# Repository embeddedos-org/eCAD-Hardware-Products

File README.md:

# eCAD Hardware Products

Hardware / PCB CAD design collection for the **EmbeddedOS (EoS)** ecosystem.
The repository organizes hardware product designs by application domain. Each
domain holds one or more product lines, and each product line typically carries
a product datasheet, a bill of materials (`bom.csv`), power-budget simulation
scripts, and placeholder directories for PCB and mechanical CAD artifacts.
Several product lines also include KiCad schematics (`*.kicad_sch`).

> Status varies by design. Directories are at different maturity levels (many
> "Design" / "Pre-production"); PCB and CAD folders often contain `.gitkeep`
> placeholders rather than finished layouts. Check each design's own `README.md`
> and `docs/` for its current state.

## Domains

The repository contains **16** domain design collections:

| Domain | Focus |
|---|---|
| `eAerospace_CAD_Design` | Aircraft components, avionics, UAV/drone systems, space systems |
| `eConsumer_CAD_Design` | Smart home devices, personal wearables, AR/smart devices |
| `eCybersecurity_CAD_Design` | Security appliances and physical security systems |
| `eDefense_CAD_Design` | Surveillance, tactical communications, protection equipment |
| `eElectronics_CAD_Design` | PCBs, embedded controllers, RF modules, FPGAs, AI accelerators |
| `eEnergy_CAD_Design` | Battery products, renewable energy systems, power electronics |
| `eHealth365_CAD_Design` | Two-device health monitoring system (smart patch / smart ring) |
| `eIndustrial_CAD_Design` | Sensors, industrial electronics, infrastructure equipment |
| `eMedical_CAD_Design` | Diagnostic, surgical, patient-care, laboratory equipment |
| `eMining_CAD_Design` | Autonomous mining/construction equipment, industrial safety systems |
| `ePAM_CAD_Design` | Personal air/ground mobility — solar-hybrid transport, 4-product line |
| `eRadar360_CAD_Design` | 360° automotive safety radar + laser + V2X + AI threat detection |
| `eRobotics_CAD_Design` | Industrial robots, autonomous systems, robot components |
| `eSmartCity_CAD_Design` | Urban infrastructure, utilities, telecommunications |
| `eTransport_CAD_Design` | Automotive electronics, rail systems, maritime systems |
| `eosHealth_CAD_Design` | Four-device wearable health platform |

Plus:

- `future_designs/` — early/prospective concepts (e.g. `eBCI-Lite`)
- `docs/` — repository-level documentation

## Typical design layout

Most domains follow a common structure, for example:

```
eAerospace_CAD_Design/
  README.md
  docs/                      business_plan.md, regulatory_path.md
  ebuild_simulation/         eBuild simulation notes
  <product_line>/
    product_datasheet.md
    bom.csv
    simulation/power_budget_sim.py
    hardware/
      pcb/  cad/  antenna/   (artifact folders; often .gitkeep placeholders)
```

Artifact formats present in the repo include Markdown datasheets, CSV BOMs,
Python simulation scripts, and KiCad schematics (`*.kicad_sch`). Some product
lines also include TypeScript/Dart companion app sources and 3D-model notes.

## Simulations

Power-budget simulations are plain Python scripts, runnable per product line:

```bash
cd eAerospace_CAD_Design/<product_line>/simulation/
python3 power_budget_sim.py
```

Design docs reference the [EoSim](https://github.com/embeddedos-org/EoSim)
digital-twin platform for hardware-in-the-loop testing. Running one script alone
does not establish that a product is validated.

## Evidence-backed product validation

The committed `tools/catalog/product_inventory.json` is the complete product
execution set. The v1 contract schemas and policy requirements are documented in
`docs/hardware-validation-contract-v1.md`.

Discover inventory drift and inspect local tool capabilities:

```bash
python3 tools/validate_products.py discover
python3 tools/validate_products.py capabilities
```

Execute V0-V4 for every inventoried product and write hash-bound receipts:

```bash
python3 tools/validate_products.py validate \
  --all \
  --output /tmp/ecad-validation \
  --mode evidence
python3 tools/validate_products.py verify-bundle \
  /tmp/ecad-validation/bundle.json
```

`--mode evidence` succeeds when the selected inventory was executed and valid
receipts were written. Individual products may still be honestly `FAIL`,
`BLOCKED`, `INCONCLUSIVE`, or `NOT_RUN`. Use `--mode gate` for a release check;
it succeeds only when every selected product has real `PASS` evidence for V0,
V1, V2, V3, and V4. Historical baseline entries never waive a failed or missing
requirement.

## License

MIT — see [LICENSE](LICENSE).

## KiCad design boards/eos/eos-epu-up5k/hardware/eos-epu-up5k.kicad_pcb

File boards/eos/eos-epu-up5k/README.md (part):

# EoS EPU Board

An original iCE40UP5K FPGA board for EPU, EmbeddedOS's RISC-V SoC: 75 × 55 mm, four layers.
Designed by Kartikeydheer Srivastava.
All rights reserved: not open source, and not under this repository's MIT licence.
Anyone may view it, clone this repository and run its tests; anything more needs
Kartikeydheer Srivastava's written permission (kartikeydheer@gmail.com). EmbeddedOS (EoS) Research Foundation has a limited, revocable
permission. See [LICENSE.txt](LICENSE.txt) and [the licence summary](../README.md#licence).

A board for the same job as a bought iCE40UP5K development board; an original design, not a copy:
no file of any vendor's board was used. No schematic, layout, CAD, Gerber or BOM of Lattice's
evaluation or breakout boards, of any other iCE40 board (iCEBreaker, UPduino, pico-ice) or of an FTDI
module was opened. The circuit comes from the chips' data sheets and application notes, the
FT2232H pin roles from the source code of the open-source programmers that use them (iceprog and
openFPGALoader), and the Pmod ports from Digilent's published Pmod Interface Specification.

| | |
|---|---|
|  |  |

One USB-C cable powers the board, programs the FPGA's configuration flash and carries EPU's serial
console. The FPGA pins are laid out for EPU's FPGA top (`epu/fpga/ice40/epu_ice40_top.v`); the
[pin table](#pin-table) maps every one of the FPGA's 39 user pins, and EPU's pin file is written from it.
EPU's source is not yet published.

## What is on it

| Block | Parts, values and source |
|---|---|
| FPGA | Lattice iCE40UP5K-SG48I (5,280 LUTs, 1 Mbit SPRAM, QFN-48 7 × 7 mm, industrial). Pins from Lattice's iCE40UP5K pinout file (Revision 1.1); everything else from the [iCE40 UltraPlus Family Data Sheet](https://www.latticesemi.com/view_document?document_id=51968) FPGA-DS-02008-2.4 ("DS") and the iCE40 Hardware Checklist FPGA-TN-02006-2.4 ("HC"). 100 nF at every supply pin and 4.7 µF per supply group (HC Table 2.2). The exposed paddle is the only ground (pinout file) and has four vias into the ground plane. |
| Power-up order | DS 4.5 and HC 2.3 ask for VCC (1.2 V) and VCCPLL first, then SPI_VCCIO1, then VPP_2V5, each after the previous one reaches 0.5 V; DS Table 4.3 asks for 0.6–10 V/ms ramps. A TI TPS22917 load switch makes the board's 3.3 V rail from the buck's output and its ON pin is the FPGA's 1.2 V rail (ON high at 1.0 V, TI SLVSDW8B), so every 3.3 V part (all FPGA banks and VPP_2V5, the flash, the FT2232H, the two oscillators) comes up after VCC: 1.2 V rises in the LDO's 550 µs start-up (≈ 2.2 V/ms), 3.3 V about 2 ms later at 1.9 V/ms (CT = 1 nF: TI SLVSDW8B 7.6). VPP_2V5 is on 3.3 V: allowed for configuration from SPI flash (2.30–3.46 V, DS Table 4.2), not for NVCM programming (≤ 3.0 V), which this board never does. QOD discharges 3.3 V through 100 Ω when 1.2 V falls, so a quick re-plug repeats the order. |
| VCCPLL | 100 Ω from VCC, 4.7 µF (HC Table 2.2's value; 100 Ω × 4.7 µF = 0.47 ms) and 100 nF at pin 29, laid as one line pin → 100 nF → 4.7 µF → 100 Ω (iCE40 sysCLOCK PLL guide FPGA-TN-02052-1.4, 5.2 and Figure 5.4; HC Table 2.2). Fitted "even if the PLL is not utilized". The SG48 has no separate PLL ground. |
| Configuration | SPI master mode from the flash. CRESET_B: 10 kΩ pull-up (it has none inside: iCE40 Programming and Configuration FPGA-TN-02001-3.5 ("TN1") 5.1) and no capacitor. DS 4.6 asks for CRESET_B low until every supply is valid, and the FPGA's own power-on reset trips far below its operating minimums (DS Table 4.4: VCC 0.79 V, SPI_VCCIO1 1.50 V), so two TI TPS3808 supervisors ([SBVS050N](https://www.ti.com/lit/ds/symlink/tps3808.pdf)) hold it low, chained as TI's Figure 7-3: U11 (TPS3808G12) watches the 1.2 V rail and holds U10's MR low; U10 (TPS3808G33) watches the 3.3 V rail and drives CRESET_B through its open-drain output. Both run from the buck's 3.3 V, which is up before either rail they watch. CRESET_B goes high 12–28 ms (CT open) after both rails are valid, and low again within about 20 µs if either sags: a brown-out reconfigures the FPGA (see [Supervisor thresholds](#supervisor-thresholds)). The CRESET button is U10's MR, so one press gives one clean, debounced pulse. CDONE: 2.2 kΩ pull-up, from TN1's `R ≤ 1 / (2 × f_config × C_CDONE)` with the default configuration clock (≤ 17 MHz, DS Table 4.24) and about 10 pF. SPI_SS_B and SPI_SCK: 10 kΩ pull-ups (HC Table 3.1; SS high selects master mode, TN1 9.3). The green DONE LED lights when CDONE is high (a 2N7002 whose gate hangs off CDONE through 10 kΩ). |
| Flash | Winbond W25Q128JVSIQ, 16 MB, SOIC-8 208 mil ([W25Q128JV data sheet](https://www.winbond.com/resource-files/w25q128jv%20revf%2003272018%20plus.pdf) Revision F). It answers the 0x0B Fast Read, 0xAB and 0xB9 commands the iCE40 uses (TN1 9.2). IQ parts have QE = 1 (7.1.4): pins 3 and 7 are IO2/IO3, held high by 10 kΩ. The bitstream (104,161 bytes, TN1 Table 9.2) sits at address 0; EPU's firmware can follow it (EPU backlog B-14). The FPGA may leave the flash in deep power-down after configuration (TN1 9.4), and iceprog powers it down after every write unless run with `-k`: **EPU's firmware must send 0xAB (release power-down) before it reads the flash.** |
| FPGA clock | X1, ECS-2520MV-120-BN-TR 12 MHz CMOS oscillator, ±50 ppm, −40 to +85 °C ([ECS-2520MV](https://ecsxtal.com/store/pdf/ECS-2520MV.pdf)), on pin 35 (IOT_46b_G0): a global input, and the GPLL pin that a PLL would use (FPGA-TN-02052 5.1.1). EPU divides it to 6 MHz. |
| USB bridge | FTDI FT2232HL ([DS_FT2232H](https://ftdichip.com/wp-content/uploads/2020/07/DS_FT2232H.pdf) Version 2.6), bus powered as its Figure 6.1: ferrite + 4.7 µF + 100 nF on VPHY and on VPLL (Table 3.2 asks for an LC filter), two 4.7 µF on VREGOUT (at least 3.3 µF, kept to −30 °C on the small-signal DC-bias curve), 100 nF on each VCORE and VCCIO pin, 12 kΩ 1 % on REF, RESET# pulled up through 1 kΩ, TEST to ground. Its 12 MHz clock is a CMOS oscillator into OSCI with OSCO open, the alternative FTDI's 6.3 gives to a crystal: X2, ECS-2520MVLC-120-CN-TR ([ECS-2520MVLC](https://ecsxtal.com/store/pdf/ECS-2520MVLC.pdf), Rev. 2022), ±25 ppm including tolerance, temperature, supply, load and reflow, plus ±3 ppm aging in the first year: ±28 ppm from −40 to +85 °C, inside FTDI's 12 MHz ± 30 ppm (Table 6.1), with no load-capacitor pulling to add (±28 ppm is the first-year figure: ECS gives aging for the first year
only). FTDI's OSCI input range is 2.97–3.63 V (Table 6.1); ECS guarantees an output high of at least
0.9 × VDD at 15 pF, which is 2.84–3.04 V on the 3.3 V rail's 3.16–3.38 V worst-case range, so a strict reading
can fall up to 0.13 V short. X2 drives one input pin through 2.7 mm of track, far below 15 pF, where a CMOS
output sits near VDD (Inferred); bring-up step 6 measures it. A crystal would also need its pullability for the budget; the stocked ±10 / ±10 ppm 12 MHz crystal (CTS 403C11A12M00000, CL 10 pF) does not publish it and is rated −20 to +70 °C only. It is a fixed-function USB bridge, not a vendor debug probe running proprietary firmware. |
| Channel A: programming | Wired as Project IceStorm's iceprog drives it (iceprog/mpsse.c and iceprog.c, commit e86829e): ADBUS0 SCK, ADBUS1 MOSI to the flash's DI, ADBUS2 MISO from the flash's DO, ADBUS4 CS, ADBUS6 CDONE (input), ADBUS7 CRESET, interface A, 6 MHz. openFPGALoader's `ice40_generic` board uses the same pins: pin-compatible, **untested** until a board passes bring-up step 9. openFPGALoader sends its first flash commands right after it pulls CRESET low, with no wait (`src/ice40.cpp` and `src/spiFlash.cpp`, commit cdfe87a); with no capacitor on CRESET_B the node falls with a time constant of about (1 kΩ ∥ 10 kΩ) × 20 pF ≈ 20 ns, far inside even one USB transfer (≥ 125 µs), and iceprog waits 250 ms anyway (`iceprog.c`). Each of these lines meets the FPGA/flash nets through 1 kΩ: when no programmer is running, channel A is in its default UART mode and drives TXD, RTS# and DTR# onto SCK, MISO and CS, which the FPGA and the flash also drive; 1 kΩ holds any such clash to 3.3 mA. **Never open channel A as a serial port; EPU's console is channel B.** An open port asserts DTR#, which pulls SPI_SS_B to 0.3 V; if the FPGA is then reconfigured (CRESET, or a brown-out) it waits as an SPI target for a bitstream from the host, and DONE stays off until the port is closed and CRESET pressed again. No passive part can prevent it: iceprog's chip select is the same low level. Once the EEPROM is programmed, setting channel A to the D2XX driver only (FTDI section 7, "Load VCP Driver" off) stops Windows from making a COM port for it. |
| Channel B: UART | BDBUS0 (TXD) to EPU's `uart_rx`, BDBUS1 (RXD) from `uart_tx`; 115,200 baud. |
| EEPROM | Microchip 93LC56BT-I/OT (DS21794G), with the pull-ups and the 2.2 kΩ of FTDI's Table 3.4 and Figure 6.1. It ships blank: the FT2232H then uses its default descriptors (VID 0403, PID 6010, both channels UART: FTDI section 7), which iceprog and openFPGALoader look for. Programmed later (FT_PROG or ftdi_eeprom), it gives the board a serial number, so several boards on one host can be told apart. |
| USB-C and protection | HRO TYPE-C-31-M-12 as a 5 V sink, 5.1 kΩ Rd on CC1 and CC2 (USB Type-C specification). TI TPD2EUSB30 on D+/D− (0.7 pF, IEC 61000-4-2 level 4, diodes to ground only: TI SLVSAC2G), low enough in capacitance for the FT2232H's high-speed lines; Littelfuse SP0503BAHTG on CC1, CC2 and VBUS (diodes to ground only). Littelfuse 0805L075WR polyfuse: 0.75 A hold at 20 °C (0.57 A at 50 °C), 1.50 A trip, R1max 0.35 Ω (0805L data sheet). VBUS carries only the buck's 4.7 µF at attach (USB 2.0 7.2.4.1: at most 10 µF). Everything is powered from VBUS, so the FT2232H is not back-powered and its D+ pull-up does not come on without VBUS **as long as no supply is fed into the 3.3 V pins of the Pmod, EXT or JTAG headers. Those pins are outputs only** (silkscreen: "3V3 PINS ARE OUTPUTS"): the load switch blocks reverse current (TI SLVSDW8B 1), so 3.3 V fed into one would run the FT2232H and the FPGA's I/O banks without VBUS and without the FPGA's 1.2 V core, against the power-up order of DS 4.5. Never power the board through them. |
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
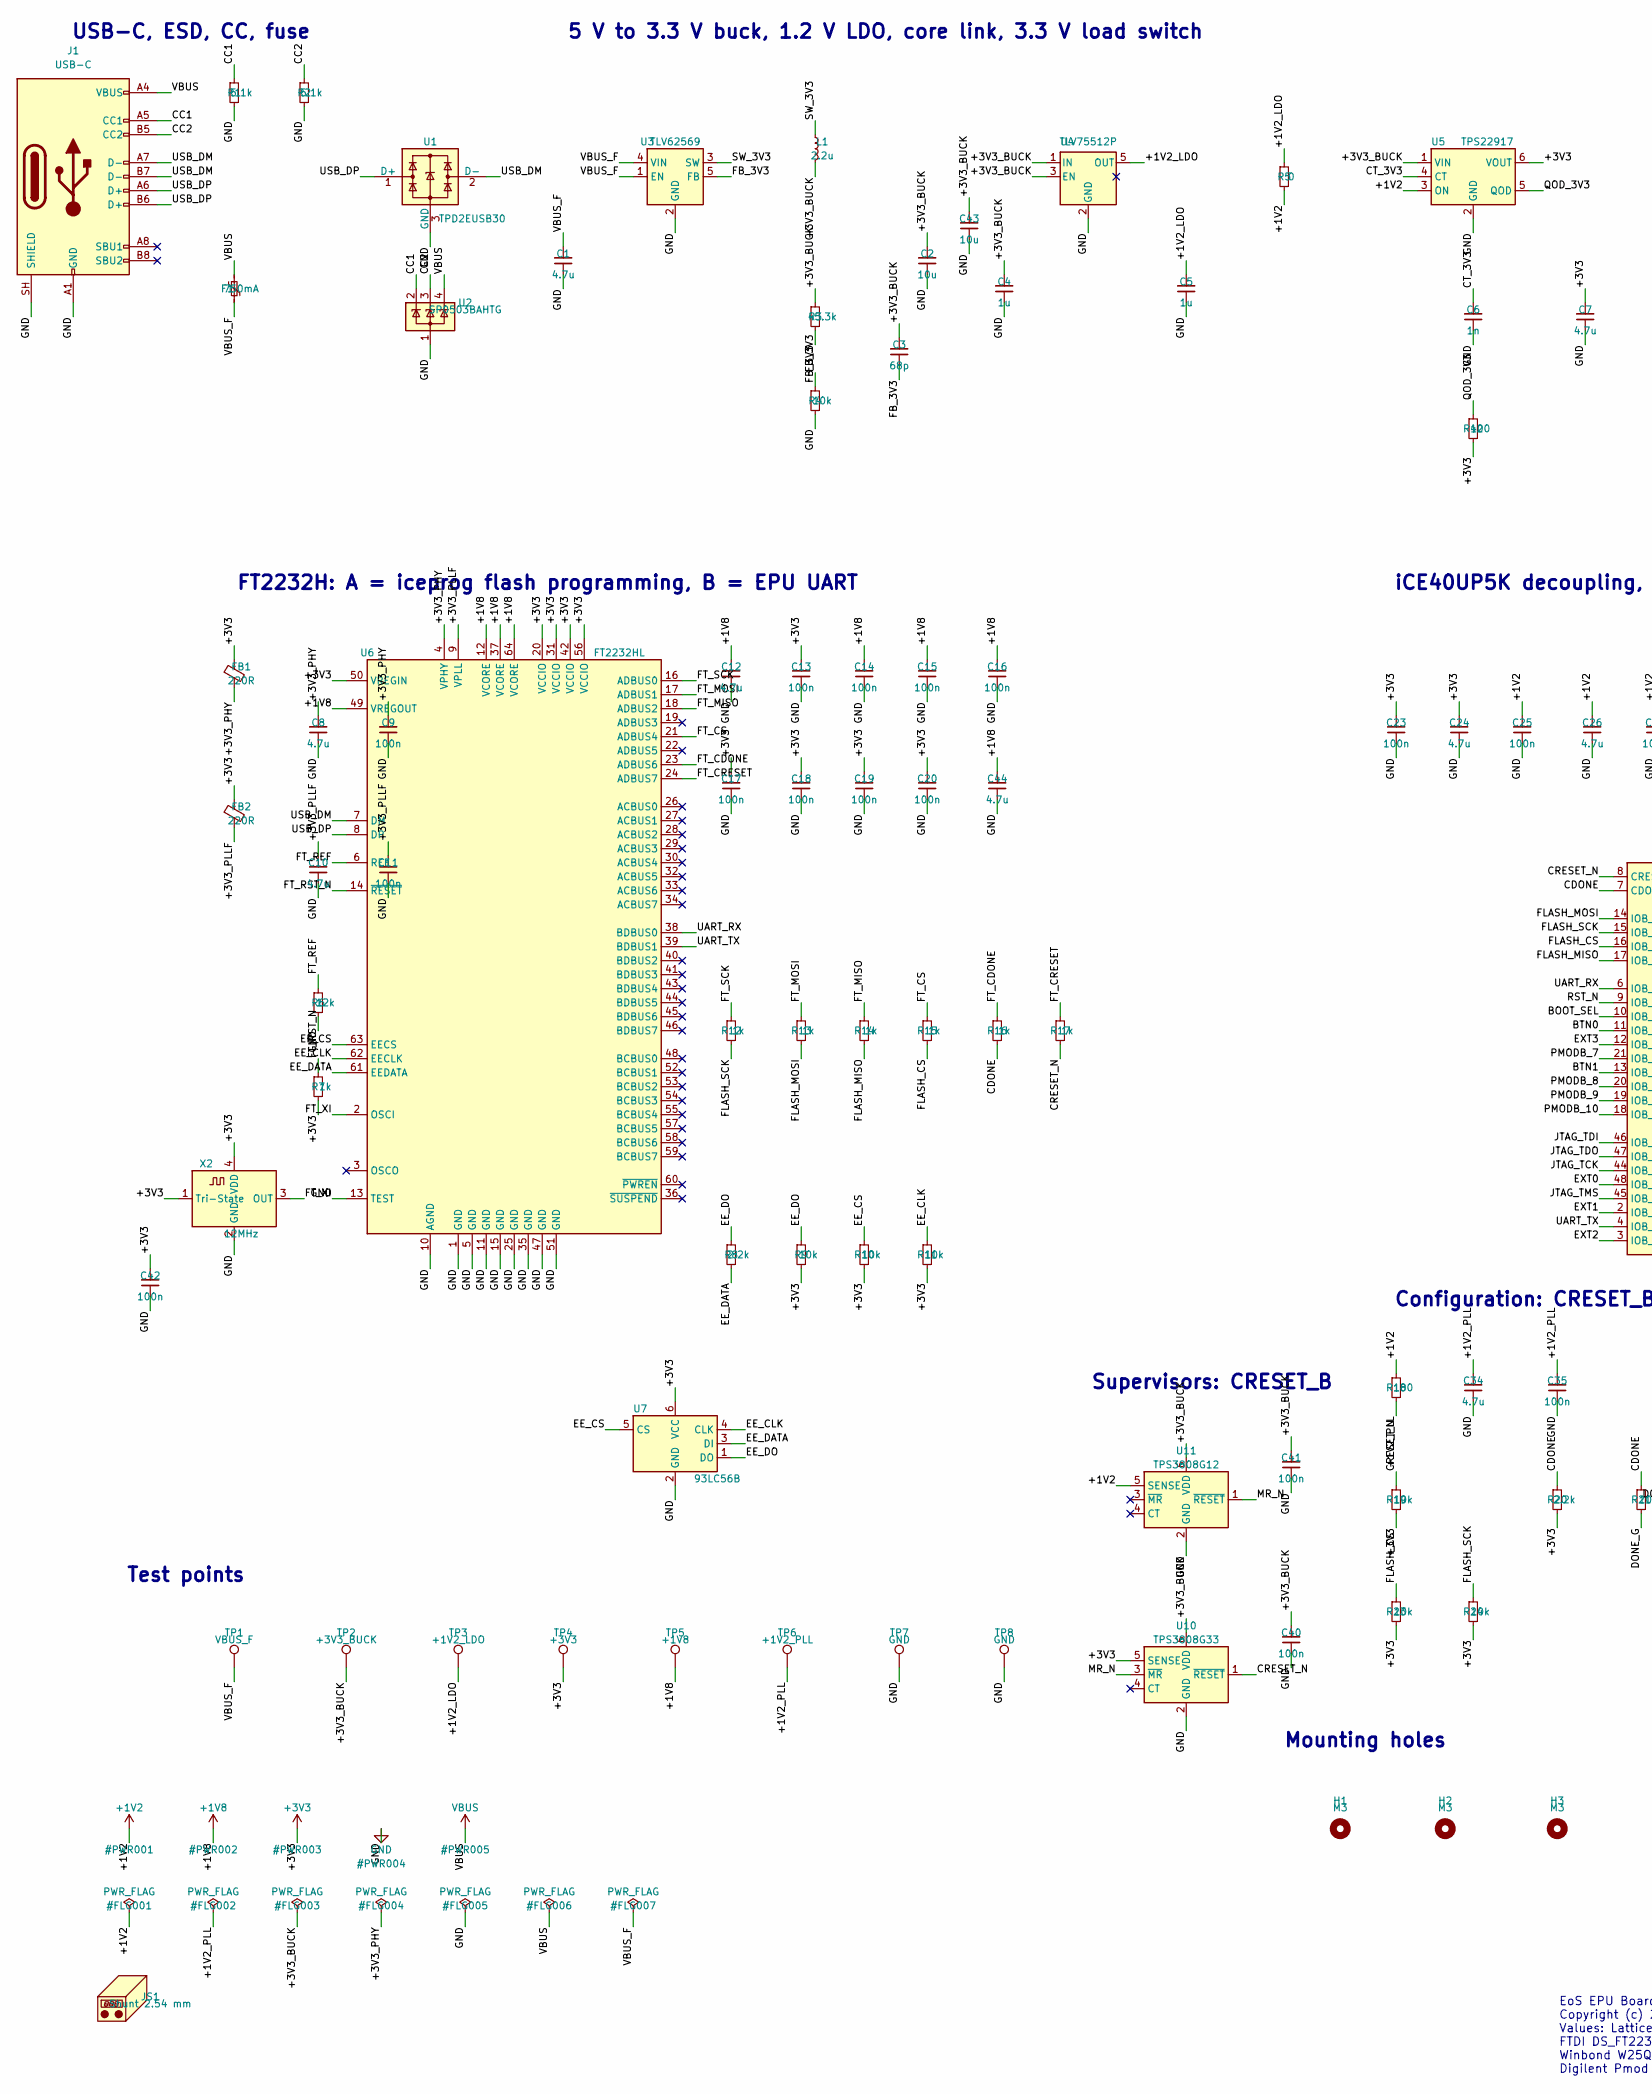
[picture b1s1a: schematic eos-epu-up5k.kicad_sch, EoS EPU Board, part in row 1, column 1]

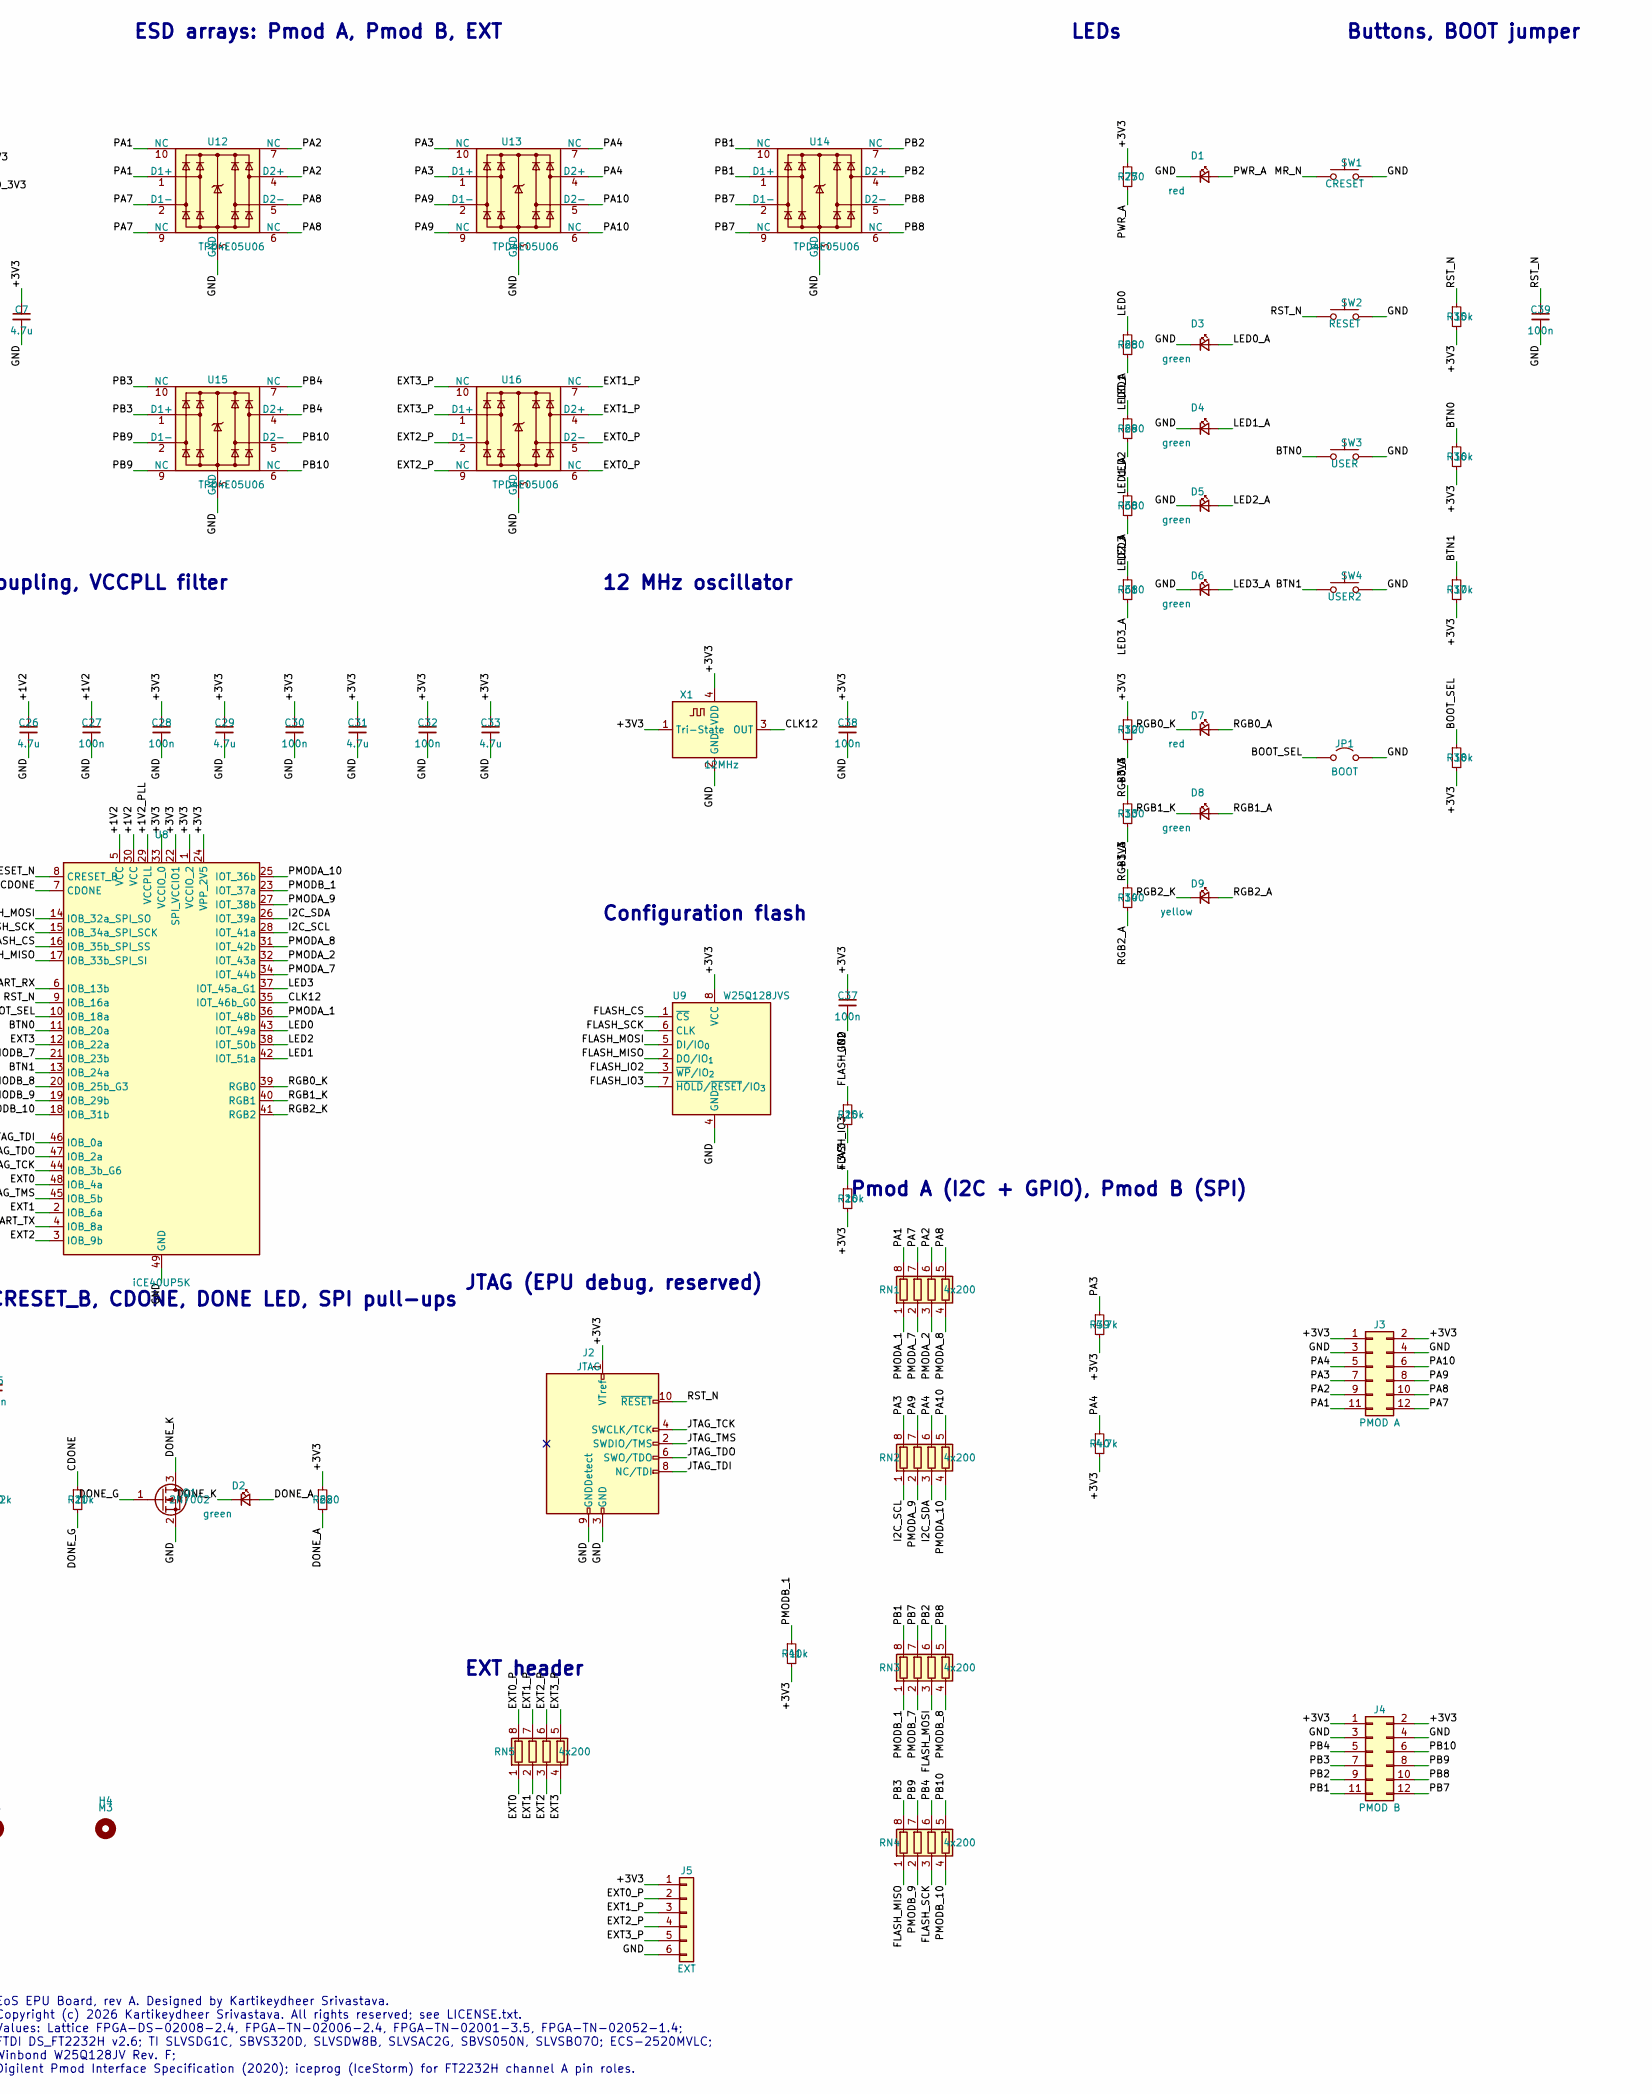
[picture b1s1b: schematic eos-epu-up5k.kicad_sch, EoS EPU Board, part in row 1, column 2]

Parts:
C1: 4.7u; C_0805_2012Metric; MPN GRM21BR71A475KE51L
C2, C43: 10u; C_0805_2012Metric; MPN GRM21BR71A106KA73L
C3: 68p; C_0402_1005Metric; MPN GRM1555C1H680JA01D
C4, C5: 1u; C_0402_1005Metric; MPN CL05A105KA5NQNC
C6: 1n; C_0402_1005Metric; MPN GRM1555C1H102JA01D
C7, C8, C10, C12, C24, C26, C29, C31, C33, C34, C44: 4.7u; C_0603_1608Metric; MPN GRM188R61C475KE11D
C9, C11, C13, C14, C15, C16, C17, C18, C19, C20, C23, C25, C27, C28, C30, C32, C35, C37, C38, C39, C40, C41, C42: 100n; C_0402_1005Metric; MPN GRM155R71C104KA88D
D1, D7: red; LED_0603_1608Metric; MPN APTD1608LSURCK
D2, D3, D4, D5, D6, D8: green; LED_0603_1608Metric; MPN APTD1608LCGCK
D9: yellow; LED_0603_1608Metric; MPN APTD1608LSYCK
F1: 750mA; Fuse_0805_2012Metric; MPN 0805L075WR
FB1, FB2: 220R; L_0603_1608Metric; MPN BLM18PG221SN1D
H1, H2, H3, H4: M3; MountingHole_3.2mm_M3
J1: USB-C; USB_C_Receptacle_HRO_TYPE-C-31-M-12; MPN TYPE-C-31-M-12
J2: JTAG; Samtec_FTSH-105-xx-x-DV_2x05_P1.27mm_Vertical_SMD; MPN FTSH-105-01-L-DV-K
J3: PMOD A; PinSocket_2x06_P2.54mm_Horizontal; MPN SSW-106-02-G-D-RA
J4: PMOD B; PinSocket_2x06_P2.54mm_Horizontal; MPN SSW-106-02-G-D-RA
J5: EXT; PinHeader_1x06_P2.54mm_Vertical; MPN TSW-106-07-G-S
JP1: BOOT; PinHeader_1x02_P2.54mm_Vertical; MPN TSW-102-07-G-S
JS1: Shunt 2.54 mm; MPN SNT-100-BK-G
L1: 2.2u; L_Coilcraft_XAL4020-XXX; MPN XAL4020-222MEC
Q1: 2N7002; SOT-23; MPN 2N7002,215
R1, R2: 5.1k; R_0402_1005Metric; MPN RC0402FR-075K1L
R3: 45.3k; R_0402_1005Metric; MPN ERA-2AEB4532X
R4: 10k; R_0402_1005Metric; MPN ERA-2AEB103X
R5: 0; R_0603_1608Metric; MPN RC0603JR-070RL
R6: 12k; R_0402_1005Metric; MPN RC0402FR-0712KL
R7, R12, R13, R14, R15, R16, R17: 1k; R_0402_1005Metric; MPN RC0402FR-071KL
R8, R20: 2.2k; R_0402_1005Metric; MPN RC0402FR-072K2L
R9, R10, R11, R19, R21, R23, R24, R25, R26, R35, R36, R37, R38, R41: 10k; R_0402_1005Metric; MPN RC0402FR-0710KL
R18, R32, R33, R34, R42: 100; R_0402_1005Metric; MPN RC0402FR-07100RL
R22, R28, R29, R30, R31: 680; R_0402_1005Metric; MPN RC0402FR-07680RL
R27: 750; R_0402_1005Metric; MPN RC0402FR-07750RL
R39, R40: 4.7k; R_0402_1005Metric; MPN RC0402FR-074K7L
RN1, RN2, RN3, RN4, RN5: 4x200; R_Array_Convex_4x0603; MPN CAY16-201J4LF
SW1: CRESET; SW_Push_1P1T_NO_CK_KMR2; MPN KMR221G LFS
SW2: RESET; SW_Push_1P1T_NO_CK_KMR2; MPN KMR221G LFS
SW3: USER; SW_Push_1P1T_NO_CK_KMR2; MPN KMR221G LFS
SW4: USER2; SW_Push_1P1T_NO_CK_KMR2; MPN KMR221G LFS
TP1: VBUS_F; TestPoint_Pad_D1.0mm
TP2: +3V3_BUCK; TestPoint_Pad_D1.0mm
TP3: +1V2_LDO; TestPoint_Pad_D1.0mm
TP4: +3V3; TestPoint_Pad_D1.0mm
TP5: +1V8; TestPoint_Pad_D1.0mm
TP6: +1V2_PLL; TestPoint_Pad_D1.0mm
TP7, TP8: GND; TestPoint_Pad_D1.0mm
U1: TPD2EUSB30; Texas_DRT-3; MPN TPD2EUSB30DRTR
U2: SP0503BAHTG; SOT-143; MPN SP0503BAHTG
U3: TLV62569; SOT-23-5; MPN TLV62569DBVR
U4: TLV75512P; SOT-23-5; MPN TLV75512PDBVR
U5: TPS22917; SOT-23-6; MPN TPS22917DBVR
U6: FT2232HL; LQFP-64_10x10mm_P0.5mm; MPN FT2232HL-REEL
U7: 93LC56B; SOT-23-6; MPN 93LC56BT-I/OT
U8: iCE40UP5K; QFN-48-1EP_7x7mm_P0.5mm_EP5.3x5.3mm; MPN ICE40UP5K-SG48I
U9: W25Q128JVS; SOIC-8_5.3x5.3mm_P1.27mm; MPN W25Q128JVSIQ
U10: TPS3808G33; SOT-23-6; MPN TPS3808G33DBVR
U11: TPS3808G12; SOT-23-6; MPN TPS3808G12DBVR
U12, U13, U14, U15, U16: TPD4E05U06; USON-10_2.5x1.0mm_P0.5mm; MPN TPD4E05U06DQAR
X1: 12MHz; Oscillator_SMD_ECS_2520MV-xxx-xx-4Pin_2.5x2.0mm; MPN ECS-2520MV-120-BN-TR
X2: 12MHz; Oscillator_SMD_ECS_2520MV-xxx-xx-4Pin_2.5x2.0mm; MPN ECS-2520MVLC-120-CN-TR

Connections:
+1V2: C25.1, C26.1, C27.1, R5.2, R18.1, U5.3 (ON), U8.5 (VCC), U8.30 (VCC), U11.5 (SENSE)
+1V8: C12.1, C14.1, C15.1, C16.1, C44.1, TP5.1, U6.12 (VCORE), U6.37 (VCORE), U6.49 (VREGOUT), U6.64 (VCORE)
+3V3: C7.1, C13.1, C17.1, C18.1, C19.1, C20.1, C23.1, C24.1, C28.1, C29.1, C30.1, C31.1, C32.1, C33.1, C37.1, C38.1, C42.1, FB1.1, FB2.1, J2.1 (VTref), J3.1, J3.2, J4.1, J4.2, J5.1, R7.2, R9.2, R10.2, R11.2, R19.2, R20.2, R22.1, R23.2, R24.2, R25.2, R26.2, R27.1, R32.1, R33.1, R34.1, R35.2, R36.2, R37.2, R38.2, R39.2, R40.2, R41.2, R42.2, TP4.1, U5.6 (VOUT), U6.20 (VCCIO), U6.31 (VCCIO), U6.42 (VCCIO), U6.50 (VREGIN), U6.56 (VCCIO), U7.6 (VCC), U8.1 (VCCIO_2), U8.22 (SPI_VCCIO1), U8.24 (VPP_2V5), U8.33 (VCCIO_0), U9.8 (VCC), U10.5 (SENSE), X1.1 (Tri-State), X1.4 (VDD), X2.1 (Tri-State), X2.4 (VDD)
/+1V2_LDO: C5.1, R5.1, TP3.1, U4.5 (OUT)
/+1V2_PLL: C34.1, C35.1, R18.2, TP6.1, U8.29 (VCCPLL)
/+3V3_BUCK: C2.1, C3.1, C4.1, C40.1, C41.1, C43.1, L1.2, R3.1, TP2.1, U4.1 (IN), U4.3 (EN), U5.1 (VIN), U10.6 (VDD), U11.6 (VDD)
/+3V3_PHY: C8.1, C9.1, FB1.2, U6.4 (VPHY)
/+3V3_PLLF: C10.1, C11.1, FB2.2, U6.9 (VPLL)
/BOOT_SEL: JP1.1 (A), R38.1, U8.10 (IOB_18a)
/BTN0: R36.1, SW3.1, U8.11 (IOB_20a)
/BTN1: R37.1, SW4.1, U8.13 (IOB_24a)
/CC1: J1.A5 (CC1), R1.1, U2.2 (K)
/CC2: J1.B5 (CC2), R2.1, U2.3 (K)
/CDONE: R16.2, R20.1, R21.1, U8.7 (CDONE)
/CLK12: U8.35 (IOT_46b_G0), X1.3 (OUT)
/CRESET_N: R17.2, R19.1, U8.8 (CRESET_B), U10.1 (~RESET)
/CT_3V3: C6.1, U5.4 (CT)
/DONE_A: D2.2 (A), R22.2
/DONE_G: Q1.1 (G), R21.2
/DONE_K: D2.1 (K), Q1.3 (D)
/EE_CLK: R11.1, U6.62 (EECLK), U7.4 (CLK)
/EE_CS: R10.1, U6.63 (EECS), U7.5 (CS)
/EE_DATA: R8.2, U6.61 (EEDATA), U7.3 (DI)
/EE_DO: R8.1, R9.1, U7.1 (DO)
/EXT0: RN5.1 (R1.1), U8.48 (IOB_4a)
/EXT0_P: J5.2, RN5.8 (R1.2), U16.5 (D2-), U16.6 (NC)
/EXT1: RN5.2 (R2.1), U8.2 (IOB_6a)
/EXT1_P: J5.3, RN5.7 (R2.2), U16.4 (D2+), U16.7 (NC)
/EXT2: RN5.3 (R3.1), U8.3 (IOB_9b)
/EXT2_P: J5.4, RN5.6 (R3.2), U16.2 (D1-), U16.9 (NC)
/EXT3: RN5.4 (R4.1), U8.12 (IOB_22a)
/EXT3_P: J5.5, RN5.5 (R4.2), U16.1 (D1+), U16.10 (NC)
/FB_3V3: C3.2, R3.2, R4.1, U3.5 (FB)
/FLASH_CS: R15.2, R23.1, U8.16 (IOB_35b_SPI_SS), U9.1 (~CS)
/FLASH_IO2: R25.1, U9.3 (~WP/IO_{2})
/FLASH_IO3: R26.1, U9.7 (~HOLD/~RESET/IO_{3})
/FLASH_MISO: R14.2, RN4.1 (R1.1), U8.17 (IOB_33b_SPI_SI), U9.2 (DO/IO_{1})
/FLASH_MOSI: R13.2, RN3.3 (R3.1), U8.14 (IOB_32a_SPI_SO), U9.5 (DI/IO_{0})
/FLASH_SCK: R12.2, R24.1, RN4.3 (R3.1), U8.15 (IOB_34a_SPI_SCK), U9.6 (CLK)
/FT_CDONE: R16.1, U6.23 (ADBUS6)
/FT_CRESET: R17.1, U6.24 (ADBUS7)
/FT_CS: R15.1, U6.21 (ADBUS4)
/FT_MISO: R14.1, U6.18 (ADBUS2)
/FT_MOSI: R13.1, U6.17 (ADBUS1)
/FT_REF: R6.1, U6.6 (REF)
/FT_RST_N: R7.1, U6.14 (~RESET)
/FT_SCK: R12.1, U6.16 (ADBUS0)
/FT_XI: U6.2 (OSCI), X2.3 (OUT)
/I2C_SCL: RN2.1 (R1.1), U8.28 (IOT_41a)
/I2C_SDA: RN2.3 (R3.1), U8.26 (IOT_39a)
/JTAG_TCK: J2.4 (SWCLK/TCK), U8.44 (IOB_3b_G6)
/JTAG_TDI: J2.8 (NC/TDI), U8.46 (IOB_0a)
/JTAG_TDO: J2.6 (SWO/TDO), U8.47 (IOB_2a)
/JTAG_TMS: J2.2 (SWDIO/TMS), U8.45 (IOB_5b)
/LED0: R28.1, U8.43 (IOT_49a)
/LED0_A: D3.2 (A), R28.2
/LED1: R29.1, U8.42 (IOT_51a)
/LED1_A: D4.2 (A), R29.2
/LED2: R30.1, U8.38 (IOT_50b)
/LED2_A: D5.2 (A), R30.2
/LED3: R31.1, U8.37 (IOT_45a_G1)
/LED3_A: D6.2 (A), R31.2
/MR_N: SW1.1, U10.3 (~MR), U11.1 (~RESET)
/PA1: J3.11, RN1.8 (R1.2), U12.1 (D1+), U12.10 (NC)
/PA2: J3.9, RN1.6 (R3.2), U12.4 (D2+), U12.7 (NC)
/PA3: J3.7, R39.1, RN2.8 (R1.2), U13.1 (D1+), U13.10 (NC)
/PA4: J3.5, R40.1, RN2.6 (R3.2), U13.4 (D2+), U13.7 (NC)
/PA7: J3.12, RN1.7 (R2.2), U12.2 (D1-), U12.9 (NC)
/PA8: J3.10, RN1.5 (R4.2), U12.5 (D2-), U12.6 (NC)
/PA9: J3.8, RN2.7 (R2.2), U13.2 (D1-), U13.9 (NC)
/PA10: J3.6, RN2.5 (R4.2), U13.5 (D2-), U13.6 (NC)
/PB1: J4.11, RN3.8 (R1.2), U14.1 (D1+), U14.10 (NC)
/PB2: J4.9, RN3.6 (R3.2), U14.4 (D2+), U14.7 (NC)
/PB3: J4.7, RN4.8 (R1.2), U15.1 (D1+), U15.10 (NC)
/PB4: J4.5, RN4.6 (R3.2), U15.4 (D2+), U15.7 (NC)
/PB7: J4.12, RN3.7 (R2.2), U14.2 (D1-), U14.9 (NC)
/PB8: J4.10, RN3.5 (R4.2), U14.5 (D2-), U14.6 (NC)
/PB9: J4.8, RN4.7 (R2.2), U15.2 (D1-), U15.9 (NC)
/PB10: J4.6, RN4.5 (R4.2), U15.5 (D2-), U15.6 (NC)
/PMODA_1: RN1.1 (R1.1), U8.36 (IOT_48b)
/PMODA_2: RN1.3 (R3.1), U8.32 (IOT_43a)
/PMODA_7: RN1.2 (R2.1), U8.34 (IOT_44b)
/PMODA_8: RN1.4 (R4.1), U8.31 (IOT_42b)
/PMODA_9: RN2.2 (R2.1), U8.27 (IOT_38b)
/PMODA_10: RN2.4 (R4.1), U8.25 (IOT_36b)
/PMODB_1: R41.1, RN3.1 (R1.1), U8.23 (IOT_37a)
/PMODB_7: RN3.2 (R2.1), U8.21 (IOB_23b)
/PMODB_8: RN3.4 (R4.1), U8.20 (IOB_25b_G3)
/PMODB_9: RN4.2 (R2.1), U8.19 (IOB_29b)
/PMODB_10: RN4.4 (R4.1), U8.18 (IOB_31b)
/PWR_A: D1.2 (A), R27.2
/QOD_3V3: R42.1, U5.5 (QOD)
/RGB0_A: D7.2 (A), R32.2
/RGB0_K: D7.1 (K), U8.39 (RGB0)
/RGB1_A: D8.2 (A), R33.2
/RGB1_K: D8.1 (K), U8.40 (RGB1)
/RGB2_A: D9.2 (A), R34.2
/RGB2_K: D9.1 (K), U8.41 (RGB2)
/RST_N: C39.1, J2.10 (~RESET), R35.1, SW2.1, U8.9 (IOB_16a)
/SW_3V3: L1.1, U3.3 (SW)
/UART_RX: U6.38 (BDBUS0), U8.6 (IOB_13b)
/UART_TX: U6.39 (BDBUS1), U8.4 (IOB_8a)
/USB_DM: J1.A7 (D-), J1.B7 (D-), U1.2 (D-), U6.7 (DM)
/USB_DP: J1.A6 (D+), J1.B6 (D+), U1.1 (D+), U6.8 (DP)
/VBUS_F: C1.1, F1.2, TP1.1, U3.1 (EN), U3.4 (VIN)
GND: C1.2, C2.2, C4.2, C5.2, C6.2, C7.2, C8.2, C9.2, C10.2, C11.2, C12.2, C13.2, C14.2, C15.2, C16.2, C17.2, C18.2, C19.2, C20.2, C23.2, C24.2, C25.2, C26.2, C27.2, C28.2, C29.2, C30.2, C31.2, C32.2, C33.2, C34.2, C35.2, C37.2, C38.2, C39.2, C40.2, C41.2, C42.2, C43.2, C44.2, D1.1 (K), D3.1 (K), D4.1 (K), D5.1 (K), D6.1 (K), J1.A1 (GND), J1.A12 (GND), J1.B1 (GND), J1.B12 (GND), J1.SH (SHIELD), J2.3 (GND), J2.5 (GND), J2.9 (GNDDetect), J3.3, J3.4, J4.3, J4.4, J5.6, JP1.2 (B), Q1.2 (S), R1.2, R2.2, R4.2, R6.2, SW1.2, SW2.2, SW3.2, SW4.2, TP7.1, TP8.1, U1.3 (GND), U2.1 (A), U3.2 (GND), U4.2 (GND), U5.2 (GND), U6.1 (GND), U6.5 (GND), U6.10 (AGND), U6.11 (GND), U6.13 (TEST), U6.15 (GND), U6.25 (GND), U6.35 (GND), U6.47 (GND), U6.51 (GND), U7.2 (GND), U8.49 (GND), U9.4 (GND), U10.2 (GND), U11.2 (GND), U12.3 (GND), U12.8 (GND), U13.3 (GND), U13.8 (GND), U14.3 (GND), U14.8 (GND), U15.3 (GND), U15.8 (GND), U16.3 (GND), U16.8 (GND), X1.2 (GND), X2.2 (GND)
VBUS: F1.1, J1.A4 (VBUS), J1.A9 (VBUS), J1.B4 (VBUS), J1.B9 (VBUS), U2.4 (K)

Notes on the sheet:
USB-C, ESD, CC, fuse
5 V to 3.3 V buck, 1.2 V LDO, core link, 3.3 V load switch
FT2232H: A = iceprog flash programming, B = EPU UART
iCE40UP5K decoupling, VCCPLL filter
Configuration: CRESET_B, CDONE, DONE LED, SPI pull-ups
Supervisors: CRESET_B
ESD arrays: Pmod A, Pmod B, EXT
12 MHz oscillator
Configuration flash
LEDs
Buttons, BOOT jumper
JTAG (EPU debug, reserved)
Pmod A (I2C + GPIO), Pmod B (SPI)
EXT header
Test points
Mounting holes
EoS EPU Board, rev A. Designed by Kartikeydheer Srivastava. Copyright (c) 2026 Kartikeydheer Srivastava. All rights reserved; see LICENSE.txt. Values: Lattice FPGA-DS-02008-2.4, FPGA-TN-02006-2.4, FPGA-TN-02001-3.5, FPGA-TN-02052-1.4; FTDI DS_FT2232H v2.6; TI SLVSDG1C, SBVS320D, SLVSDW8B, SLVSAC2G,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

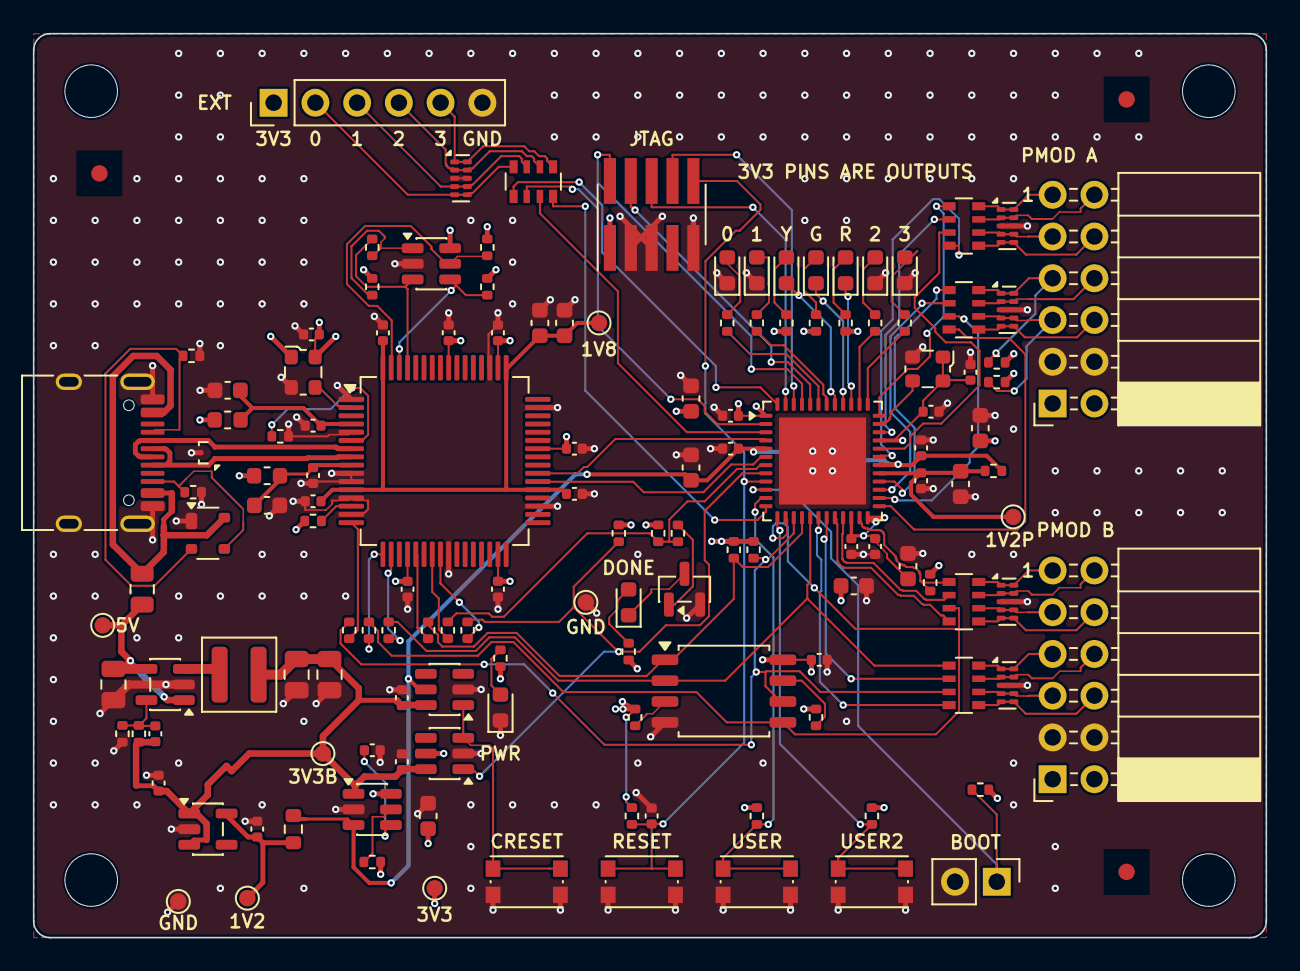
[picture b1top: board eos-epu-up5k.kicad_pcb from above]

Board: 4 copper layers, 75.0 x 55.0 mm, 145 parts (0 on the bottom side), 107 nets.

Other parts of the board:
FID1, FID2, FID3: Fiducial; Fiducial_1mm_Mask2mm

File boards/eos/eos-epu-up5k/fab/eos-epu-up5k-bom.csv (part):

"Refs","Value","Footprint","Manufacturer","MPN","Description","Assembly","Qty","DNP"
"C1","4.7u","Capacitor_SMD:C_0805_2012Metric","Murata","GRM21BR71A475KE51L","Capacitor 4.7 uF 10 V X7R 0805 (buck input, at VIN and GND: TI SLVSDG1C 8.2.2.5, 10.1)","","1",""
"C2,C43","10u","Capacitor_SMD:C_0805_2012Metric","Murata","GRM21BR71A106KA73L","Capacitor 10 uF 10 V X7R 0805 (buck output, in parallel with C2),Capacitor 10 uF 10 V X7R 0805 (buck output, with C43: TI SLVSDG1C Table 4, 2.2 uH, 10-47 uF; >= 5 uF effective: 2 x 4.53 uF at 3.3 V, -30 C, 0.01 Vrms)","","2",""
"C3","68p","Capacitor_SMD:C_0402_1005Metric","Murata","GRM1555C1H680JA01D","Capacitor 68 pF C0G 0402 (feed-forward across R1: TI's 6.8 pF for R2 = 100 kohm, same R1 x C3)","","1",""
"C4,C5","1u","Capacitor_SMD:C_0402_1005Metric","Samsung Electro-Mechanics","CL05A105KA5NQNC","Capacitor 1 uF 25 V X5R 0402 (LDO input, at least 1 uF: TI SBVS320D 5.3),Capacitor 1 uF 25 V X5R 0402 (LDO output, at least 1 uF: TI SBVS320D 5.3)","","2",""
"C6","1n","Capacitor_SMD:C_0402_1005Metric","Murata","GRM1555C1H102JA01D","Capacitor 1 nF C0G 50 V 0402 (CT: tR 1.6 ms, 1.9 V/ms at 3.3 V, TI SLVSDW8B 7.6; >= 7 V rating, 7.3)","","1",""
"C7,C8,C10,C12,C24,C26,C29,C31,C33,C34,C44","4.7u","Capacitor_SMD:C_0603_1608Metric","Murata","GRM188R61C475KE11D","Capacitor 4.7 uF 16 V X5R 0603 (3.3 V rail bulk after the load switch),Capacitor 4.7 uF 16 V X5R 0603 (SPI_VCCIO1 group: Lattice FPGA-TN-02006-2.4 Table 2.2),Capacitor 4.7 uF 16 V X5R 0603 (VCC group: Lattice FPGA-TN-02006-2.4 Table 2.2),Capacitor 4.7 uF 16 V X5R 0603 (VCCIO_0 group: Lattice FPGA-TN-02006-2.4 Table 2.2),Capacitor 4.7 uF 16 V X5R 0603 (VCCIO_2 group: Lattice FPGA-TN-02006-2.4 Table 2.2),Capacitor 4.7 uF 16 V X5R 0603 (VCCPLL CLF: Lattice FPGA-TN-02052-1.4 Figure 5.4; Lattice FPGA-TN-02006-2.4 Table 2.2 value, 100 ohm x 4.7 uF = 0.47 ms),Capacitor 4.7 uF 16 V X5R 0603 (VPHY pin 4: FTDI DS_FT2232H v2.6 Figure 6.1),Capacitor 4.7 uF 16 V X5R 0603 (VPLL pin 9: FTDI DS_FT2232H v2.6 Figure 6.1),Capacitor 4.7 uF 16 V X5R 0603 (VPP_2V5 group: Lattice FPGA-TN-02006-2.4 Table 2.2),Capacitor 4.7 uF 16 V X5R 0603 (VREGOUT pin 49, with C44: at least 3.3 uF, FTDI DS_FT2232H v2.6 Table 3.2; 2 x 2.81 uF at 1.8 V, -30 C, 0.01 Vrms),Capacitor 4.7 uF 16 V X5R 0603 (VREGOUT, in parallel with C12)","","11",""
"C9,C11,C13-C20,C23,C25,C27,C28,C30,C32,C35,C37-C42","100n","Capacitor_SMD:C_0402_1005Metric","Murata","GRM155R71C104KA88D","Capacitor 100 nF X7R 0402 (FT2232H oscillator X2 VDD),Capacitor 100 nF X7R 0402 (SPI_VCCIO1 pin 22: Lattice FPGA-TN-02006-2.4 Table 2.2),Capacitor 100 nF X7R 0402 (U10 VDD: TI SBVS050N 5, 0.1 uF at the pin),Capacitor 100 nF X7R 0402 (U11 VDD: TI SBVS050N 5, 0.1 uF at the pin),Capacitor 100 nF X7R 0402 (VCC pin 30: Lattice FPGA-TN-02006-2.4 Table 2.2),Capacitor 100 nF X7R 0402 (VCC pin 5: Lattice FPGA-TN-02006-2.4 Table 2.2),Capacitor 100 nF X7R 0402 (VCCIO pin 20: FTDI DS_FT2232H v2.6 Figure 6.1),Capacitor 100 nF X7R 0402 (VCCIO pin 31: FTDI DS_FT2232H v2.6 Figure 6.1),Capacitor 100 nF X7R 0402 (VCCIO pin 42: FTDI DS_FT2232H v2.6 Figure 6.1),Capacitor 100 nF X7R 0402 (VCCIO pin 56: FTDI DS_FT2232H v2.6 Figure 6.1),Capacitor 100 nF X7R 0402 (VCCIO_0 pin 33: Lattice FPGA-TN-02006-2.4 Table 2.2),Capacitor 100 nF X7R 0402 (VCCIO_2 pin 1: Lattice FPGA-TN-02006-2.4 Table 2.2),Capacitor 100 nF X7R 0402 (VCCPLL CHF at pin 29: Lattice FPGA-TN-02052-1.4 Figure 5.4),Capacitor 100 nF X7R 0402 (VCORE pin 12: FTDI DS_FT2232H v2.6 Figure 6.1),Capacitor 100 nF X7R 0402 (VCORE pin 37: FTDI DS_FT2232H v2.6 Figure 6.1),Capacitor 100 nF X7R 0402 (VCORE pin 64: FTDI DS_FT2232H v2.6 Figure 6.1),Capacitor 100 nF X7R 0402 (VPHY pin 4: FTDI DS_FT2232H v2.6 Figure 6.1),Capacitor 100 nF X7R 0402 (VPLL pin 9: FTDI DS_FT2232H v2.6 Figure 6.1),Capacitor 100 nF X7R 0402 (VPP_2V5 pin 24: Lattice FPGA-TN-02006-2.4 Table 2.2),Capacitor 100 nF X7R 0402 (VREGIN pin 50: FTDI DS_FT2232H v2.6 Figure 6.1),Capacitor 100 nF X7R 0402 (flash VCC),Capacitor 100 nF X7R 0402 (oscillator VDD),Capacitor 100 nF X7R 0402 (reset filter: 1 ms with 10 kohm, BENCH-READY D5; EPU synchronises it)","","23",""
"D1,D7","red","LED_SMD:LED_0603_1608Metric","Kingbright","APTD1608LSURCK","LED red 0603 (DSAO7433, VF 1.75 V typ at 2 mA): on RGB0 (pin 39), a 24 mA open-drain sink,LED red 0603 (DSAO7433, VF 1.75 V typ at 2 mA): power, on the 3.3 V rail","","2",""
"D2-D6,D8","green","LED_SMD:LED_0603_1608Metric","Kingbright","APTD1608LCGCK","LED green 0603 (DSAO7432, VF 1.9 V typ at 2 mA): DONE, lit once the FPGA has configured (CDONE high),LED green 0603 (DSAO7432, VF 1.9 V typ at 2 mA): on RGB1 (pin 40), a 24 mA open-drain sink,LED green 0603 (DSAO7432, VF 1.9 V typ at 2 mA): user LED 0, EPU gpio[0],LED green 0603 (DSAO7432, VF 1.9 V typ at 2 mA): user LED 1, EPU gpio[1],LED green 0603 (DSAO7432, VF 1.9 V typ at 2 mA): user LED 2, EPU gpio[2],LED green 0603 (DSAO7432, VF 1.9 V typ at 2 mA): user LED 3, EPU gpio[3]","","6",""
"D9","yellow","LED_SMD:LED_0603_1608Metric","Kingbright","APTD1608LSYCK","LED yellow 0603 (DSAO7434, VF 1.85 V typ at 2 mA): on RGB2 (pin 41), a 24 mA open-drain sink","","1",""
"F1","750mA","Fuse:Fuse_0805_2012Metric","Littelfuse","0805L075WR","PTC fuse 0.75 A hold (0.57 A at 50 C), 1.50 A trip, 6 V, R1max 0.35 ohm, 0805 (Littelfuse 0805L, revised 10/29/21)","","1",""
"FB1,FB2","220R","Inductor_SMD:L_0603_1608Metric","Murata","BLM18PG221SN1D","Ferrite bead 220 ohm at 100 MHz, 1.4 A, 0.10 ohm max, 0603 (Murata): VPHY filter (FTDI DS_FT2232H v2.6 Table 3.2, Figure 6.1),Ferrite bead 220 ohm at 100 MHz, 1.4 A, 0.10 ohm max, 0603 (Murata): VPLL filter (FTDI DS_FT2232H v2.6 Table 3.2, Figure 6.1)","","2",""
"J1","USB-C","Connector_USB:USB_C_Receptacle_HRO_TYPE-C-31-M-12","Korean Hroparts","TYPE-C-31-M-12","USB-C 2.0 receptacle, 16 pins, 5 V sink: power, FT2232H channel A (programming) and B (UART)","","1",""
"J2","JTAG","EoS_Packages:Samtec_FTSH-105-xx-x-DV_2x05_P1.27mm_Vertical_SMD","Samtec","FTSH-105-01-L-DV-K","JTAG header, Arm 10-pin 1.27 mm layout (VTref, TMS, TCK, TDO, TDI, nRESET): EPU's planned debug port","","1",""
"J3","PMOD A","Connector_PinSocket_2.54mm:PinSocket_2x06_P2.54mm_Horizontal","Samtec","SSW-106-02-G-D-RA","Pmod A host port, 2x6 2.54 mm right-angle socket: 1 INT (gpio[7]), 2 GPIO, 3 SCL, 4 SDA, 7-10 GPIO, 5/11 GND, 6/12 3.3 V (Digilent Pmod Interface Specification (2020-10-28) 5.5 Type 6A)","","1",""
"J4","PMOD B","Connector_PinSocket_2.54mm:PinSocket_2x06_P2.54mm_Horizontal","Samtec","SSW-106-02-G-D-RA","Pmod B host port, 2x6 2.54 mm right-angle socket: 1 CS (spi_cs_n[1]), 2 MOSI, 3 MISO, 4 SCK, 7 INT (gpio[5]), 8 RESET (gpio[6]), 9 CS2, 10 CS3 (Digilent Pmod Interface Specification (2020-10-28) 5.2 Type 2A)","","1",""
"J5","EXT","Connector_PinHeader_2.54mm:PinHeader_1x06_P2.54mm_Vertical","Samtec","TSW-106-07-G-S","Header 1x6 2.54 mm: 3.3 V (an output), EXT0-EXT3 (FPGA pins 48, 2, 3, 12 via 200 ohm, ESD array U16), GND (Samtec TSW)","","1",""
"JP1","BOOT","Connector_PinHeader_2.54mm:PinHeader_1x02_P2.54mm_Vertical","Samtec","TSW-102-07-G-S","Header 1x2 2.54 mm: BOOT strap, open = boot_sel 1, shunt fitted = 0 (Samtec TSW)","","1",""
"JS1","Shunt 2.54 mm","","Samtec","SNT-100-BK-G","Jumper shunt, 2.54 mm, 2 positions, gold, supplied for JP1 (1); where to fit them: the README. Second source: Sullins QPC02SXGN-RC","Loose: supplied with the board, not placed","1",""
"L1","2.2u","Inductor_SMD:L_Coilcraft_XAL4020-XXX","Coilcraft","XAL4020-222MEC","Inductor 2.2 uH, DCR 38.7 mohm max, Isat 5.6 A, -40 to +125 C (Coilcraft 806-1, packaging code C; TI SLVSDG1C Table 3 L1)","","1",""
"Q1","2N7002","Package_TO_SOT_SMD:SOT-23","Nexperia","2N7002,215","N-MOSFET 60 V 300 mA, VGS(th) 1-2.5 V, Ciss 50 pF max (Nexperia 2N7002 Rev. 7): lights DONE when CDONE is high","","1",""
"R1,R2","5.1k","Resistor_SMD:R_0402_1005Metric","Yageo","RC0402FR-075K1L","Resistor 5.1k 1% 0402 (CC1 Rd: a USB Type-C sink),Resistor 5.1k 1% 0402 (CC2 Rd: a USB Type-C sink)","","2",""
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

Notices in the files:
boards/eos/eos-epu-up5k/hardware/eos-epu-up5k.kicad_pcb:
Copyright (c) 2026 Kartikeydheer Srivastava. Licence: All rights reserved
All rights reserved: see LICENSE.txt; permission from kartikeydheer@gmail.com
boards/eos/eos-epu-up5k/hardware/eos-epu-up5k.kicad_sch:
FT2232H channel A pin roles: from Project IceStorm's iceprog source (ISC licence) and openFPGALoader's board table (Apache-2.0), used as facts only; no code copied
boards/eos/eos-learn-rp2350/hardware/eos-learn-rp2350.kicad_pcb:
Core layout (c) 2026 Raspberry Pi Ltd  MIT
